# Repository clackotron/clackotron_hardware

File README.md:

# Clackotron 2000 - Hardware
This repository contains the hardware for the Clackotron 2000 project, which provides a simple, all-in-one solution for controlling SBB split-flap modules. For more information on the project in general, visit the [docs repository](https://github.com/clackotron/clackotron_docs).

The hardware is based around an ESP32-S3 and designed in KiCAD 9.x. The production files can be used to easily order the latest version of the PCB from a manufacturer. (JLCPCB)

Most notably, the hardware contains:
* 30V DC input and +/-/A/B connector (same as SBB split flap modules).
* Internal power supply for 5V (RS485) and 3.3V (ESP32-S3).
* An ESP32-S3 on which the [firmware](https://github.com/clackotron/clackotron_firmware) and [webinterface](https://github.com/clackotron/clackotron_webinterface) will run.
* A level converter for sending/receiving RS485 from the ESP32-S3.
* An RTC (PCF85263A) and battery for time-keeping while offline.
* Two buttons and a RGB-Led for misc. functionality.

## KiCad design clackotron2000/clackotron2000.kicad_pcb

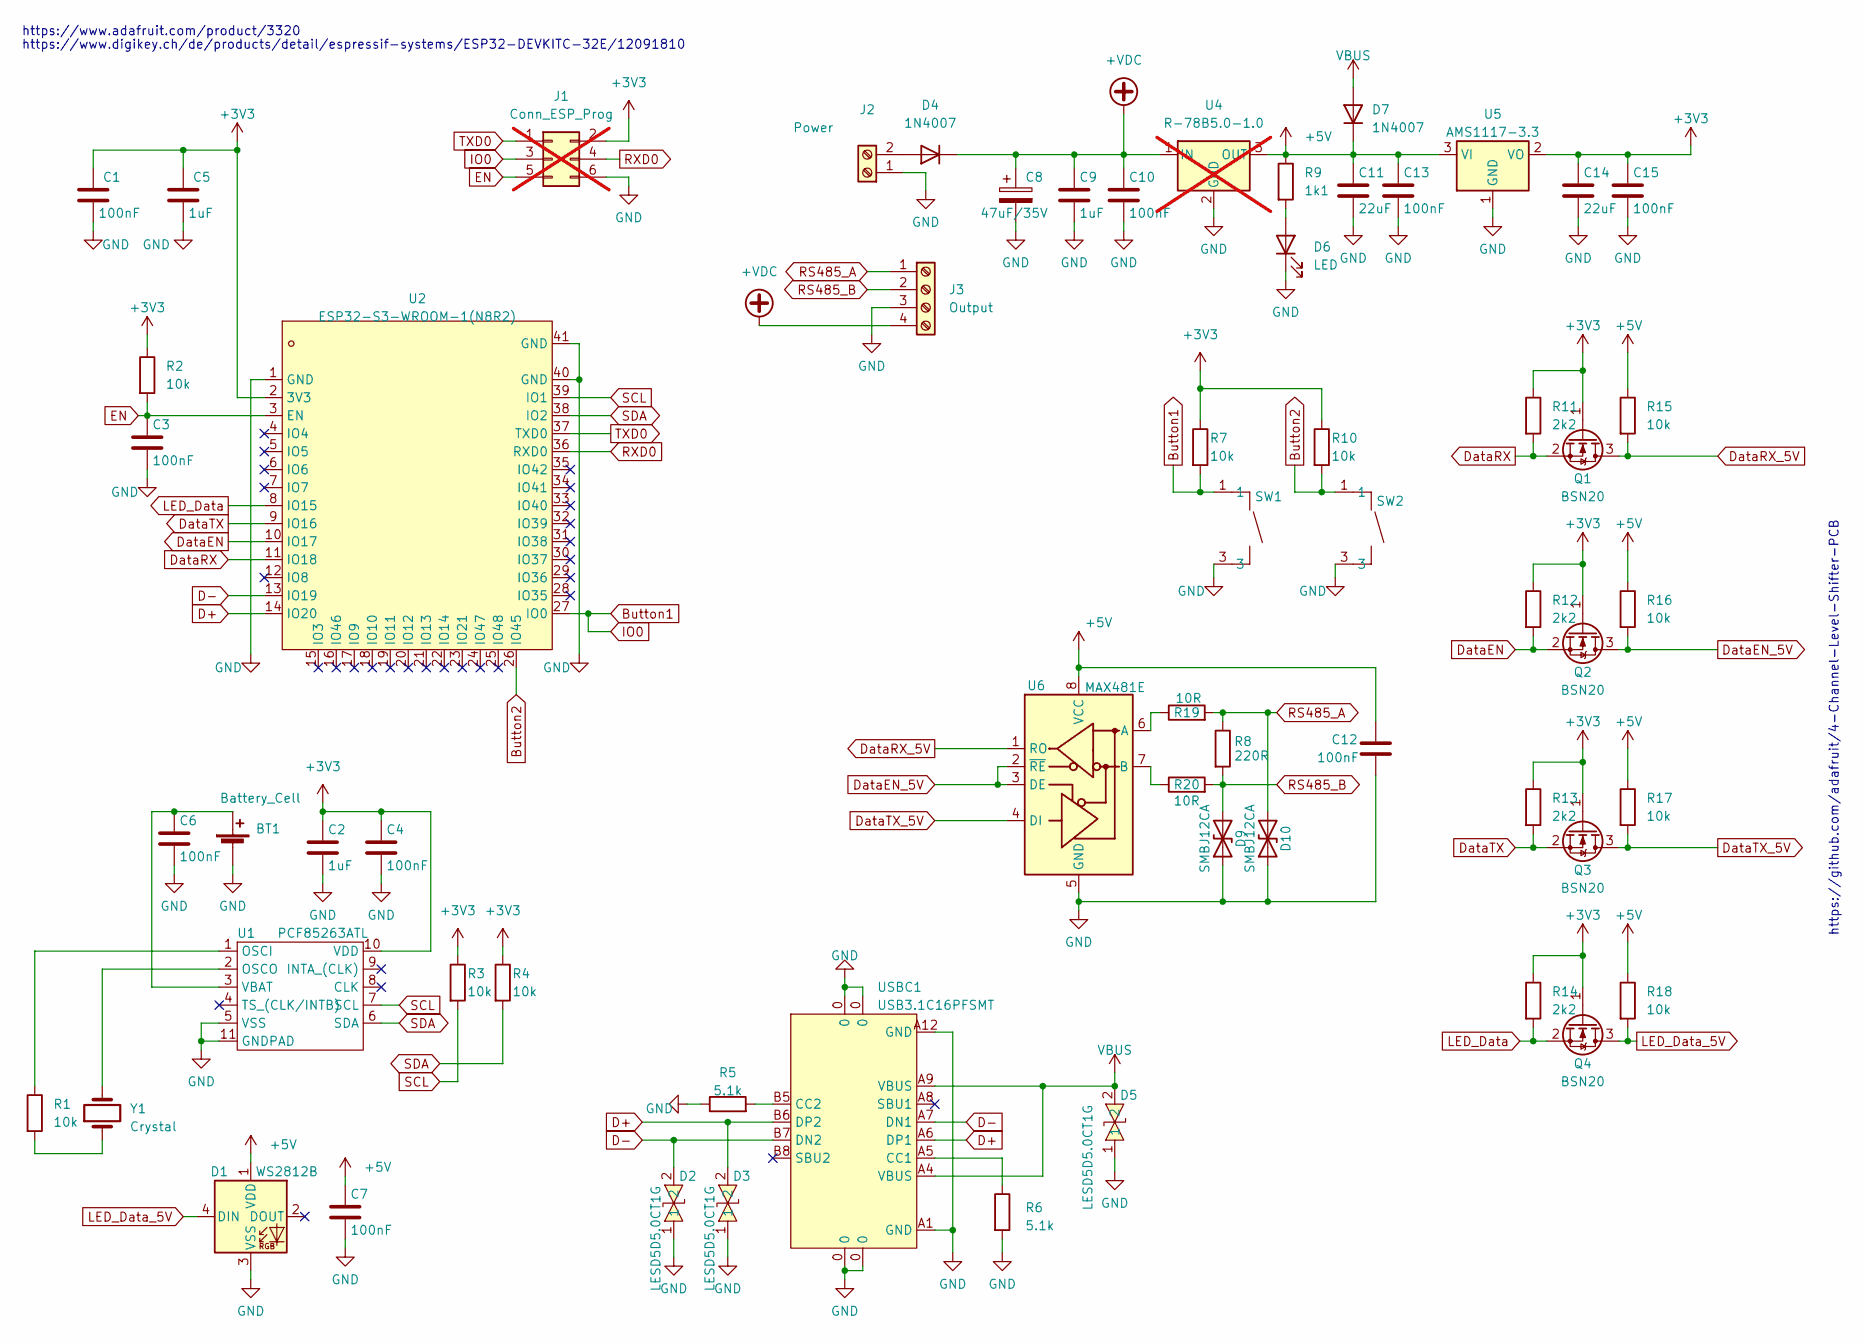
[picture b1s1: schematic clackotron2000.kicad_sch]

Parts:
BT1: Battery_Cell; BAT-SMD_MYOUNG_MY-2032-04; LCSC Part # C964837
C1, C3, C4, C6, C7, C10, C12, C13, C15: 100nF; C_0805_2012Metric; LCSC Part # C49678
C2, C5, C9: 1uF; C_0805_2012Metric; LCSC Part # C28323
C8: 47uF/35V; CAP-SMD_BD6.3-L6.6-W6.6-LS7.2-FD; LCSC Part # C3344
C11, C14: 22uF; C_1206_3216Metric; LCSC Part # C12891
D1: WS2812B; LED_WS2812B_PLCC4_5.0x5.0mm_P3.2mm; LCSC Part # C2761795
D2, D3, D5: LESD5D5.0CT1G; SOD-523_L1.2-W0.8-LS1.6-BI; LCSC Part C383211
D4, D7: 1N4007; D_SMA; LCSC Part # C2909831
D6: LED; LED_0805_2012Metric; LCSC Part # C84256
D9, D10: SMBJ12CA; D_SMB; LCSC Part C83849
J1: Conn_ESP_Prog; PinHeader_2x03_P2.54mm_Vertical; not fitted
J2: Power; TerminalBlock_4Ucon_1x02_P3.50mm_Horizontal; LCSC Part # C466970
J3: Output; TerminalBlock_4Ucon_1x04_P3.50mm_Horizontal; LCSC Part # C557656
Q1, Q2, Q3, Q4: BSN20; SOT-23; LCSC Part # C116157
R1, R2, R3, R4, R7, R10, R15, R16, R17, R18: 10k; R_0805_2012Metric; LCSC Part # C17414
R5, R6: 5.1k; R_0805_2012Metric; LCSC Part # C204548
R8: 220R; R_1206_3216Metric; LCSC Part # C17957
R9: 1k1; R_0805_2012Metric; LCSC Part # C325794
R11, R12, R13, R14: 2k2; R_0805_2012Metric; LCSC Part # C17520
R19, R20: 10R; R_1206_3216Metric; LCSC Part # C840609
SW1, SW2: K2-1102SP-C4SC-04; KEY-SMD_4P-L6.0-W6.0-P4.50-LS9.5-BL; LCSC Part C127509
U1: PCF85263ATL; DFN-10-1EP_2.6x2.6mm_P0.5mm_EP1.3x2.2mm; LCSC Part C2651523
U2: ESP32-S3-WROOM-1(N8R2); WIRELM-SMD_ESP32-S3-WROOM-1; LCSC Part C2913204
U4: R-78B5.0-1.0; Converter_DCDC_RECOM_R-78E-0.5_THT; digikey 945-R-78K5.0-1.0-ND; not fitted
U5: AMS1117-3.3; SOT-223-3_TabPin2; LCSC Part # C369933
U6: MAX481E; SOIC-8_3.9x4.9mm_P1.27mm; LCSC Part C41369525
USBC1: USB3.1C16PFSMT; USB-C-SMD_TYPE-C-USB-17; LCSC Part C167321
Y1: Crystal; Crystal_SMD_3215-2Pin_3.2x1.5mm; LCSC Part # C130253

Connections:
+3V3: C1.1, C2.1, C4.1, C5.1, C14.1, C15.1, J1.2, Q1.1 (G), Q2.1 (G), Q3.1 (G), Q4.1 (G), R2.1, R3.1, R4.1, R7.1, R10.1, R11.1, R12.1, R13.1, R14.1, U1.10 (VDD), U2.2 (3V3), U5.2 (VO)
+5V: C7.1, C11.1, C12.1, C13.1, D1.1 (VDD), D7.1 (K), R9.1, R15.1, R16.1, R17.1, R18.1, U4.3 (OUT), U5.3 (VI), U6.8 (VCC)
+VDC: C8.1, C9.1, C10.1, D4.1 (K), J3.4, U4.1 (IN)
Button1: J1.3, R7.2, SW1.1, SW1.2, U2.27 (IO0)
Button2: R10.2, SW2.1, SW2.2, U2.26 (IO45)
D+: D3.2, U2.14 (IO20), USBC1.A6 (DP1), USBC1.B6 (DP2)
D-: D2.2, U2.13 (IO19), USBC1.A7 (DN1), USBC1.B7 (DN2)
DataEN: Q2.2 (S), R12.2, U2.10 (IO17)
DataEN_5V: Q2.3 (D), R16.2, U6.2 (~RE), U6.3 (DE)
DataRX: Q1.2 (S), R11.2, U2.11 (IO18)
DataRX_5V: Q1.3 (D), R15.2, U6.1 (RO)
DataTX: Q3.2 (S), R13.2, U2.9 (IO16)
DataTX_5V: Q3.3 (D), R17.2, U6.4 (DI)
EN: C3.1, J1.5, R2.2, U2.3 (EN)
GND: BT1.2 (-), C1.2, C2.2, C3.2, C4.2, C5.2, C6.2, C7.2, C8.2, C9.2, C10.2, C11.2, C12.2, C13.2, C14.2, C15.2, D1.3 (VSS), D2.1, D3.1, D5.1, D6.1 (K), D9.1 (A1), D10.1 (A1), J1.6, J2.1, J3.3, R5.1, R6.2, SW1.3, SW1.4, SW2.3, SW2.4, U1.5 (VSS), U1.11 (GNDPAD), U2.1 (GND), U2.40 (GND), U2.41 (GND), U4.2 (GND), U5.1 (GND), U6.5 (GND), USBC1.0, USBC1.A1 (GND), USBC1.A12 (GND)
LED_Data: Q4.2 (S), R14.2, U2.8 (IO15)
LED_Data_5V: D1.4 (DIN), Q4.3 (D), R18.2
unnamed: BT1.1 (+), C6.1, U1.3 (VBAT)
unnamed: D4.2 (A), J2.2
unnamed: D6.2 (A), R9.2
unnamed: R1.2, Y1.1
unnamed: R1.1, U1.1 (OSCI)
unnamed: U1.2 (OSCO), Y1.2
unnamed: R19.1, U6.6 (A)
unnamed: R20.1, U6.7 (B)
unnamed: R6.1, USBC1.A5 (CC1)
unnamed: R5.2, USBC1.B5 (CC2)
RS485_A: D10.2 (A2), J3.1, R8.1, R19.2
RS485_B: D9.2 (A2), J3.2, R8.2, R20.2
RXD0: J1.4, U2.36 (RXD0)
SCL: R3.2, U1.7 (SCL), U2.39 (IO1)
SDA: R4.2, U1.6 (SDA), U2.38 (IO2)
TXD0: J1.1, U2.37 (TXD0)
VBUS: D5.2, D7.2 (A), USBC1.A4 (VBUS), USBC1.A9 (VBUS)

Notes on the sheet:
https://github.com/adafruit/4-Channel-Level-Shifter-PCB
https://www.adafruit.com/product/3320
https://www.digikey.ch/de/products/detail/espressif-systems/ESP32-DEVKITC-32E/12091810

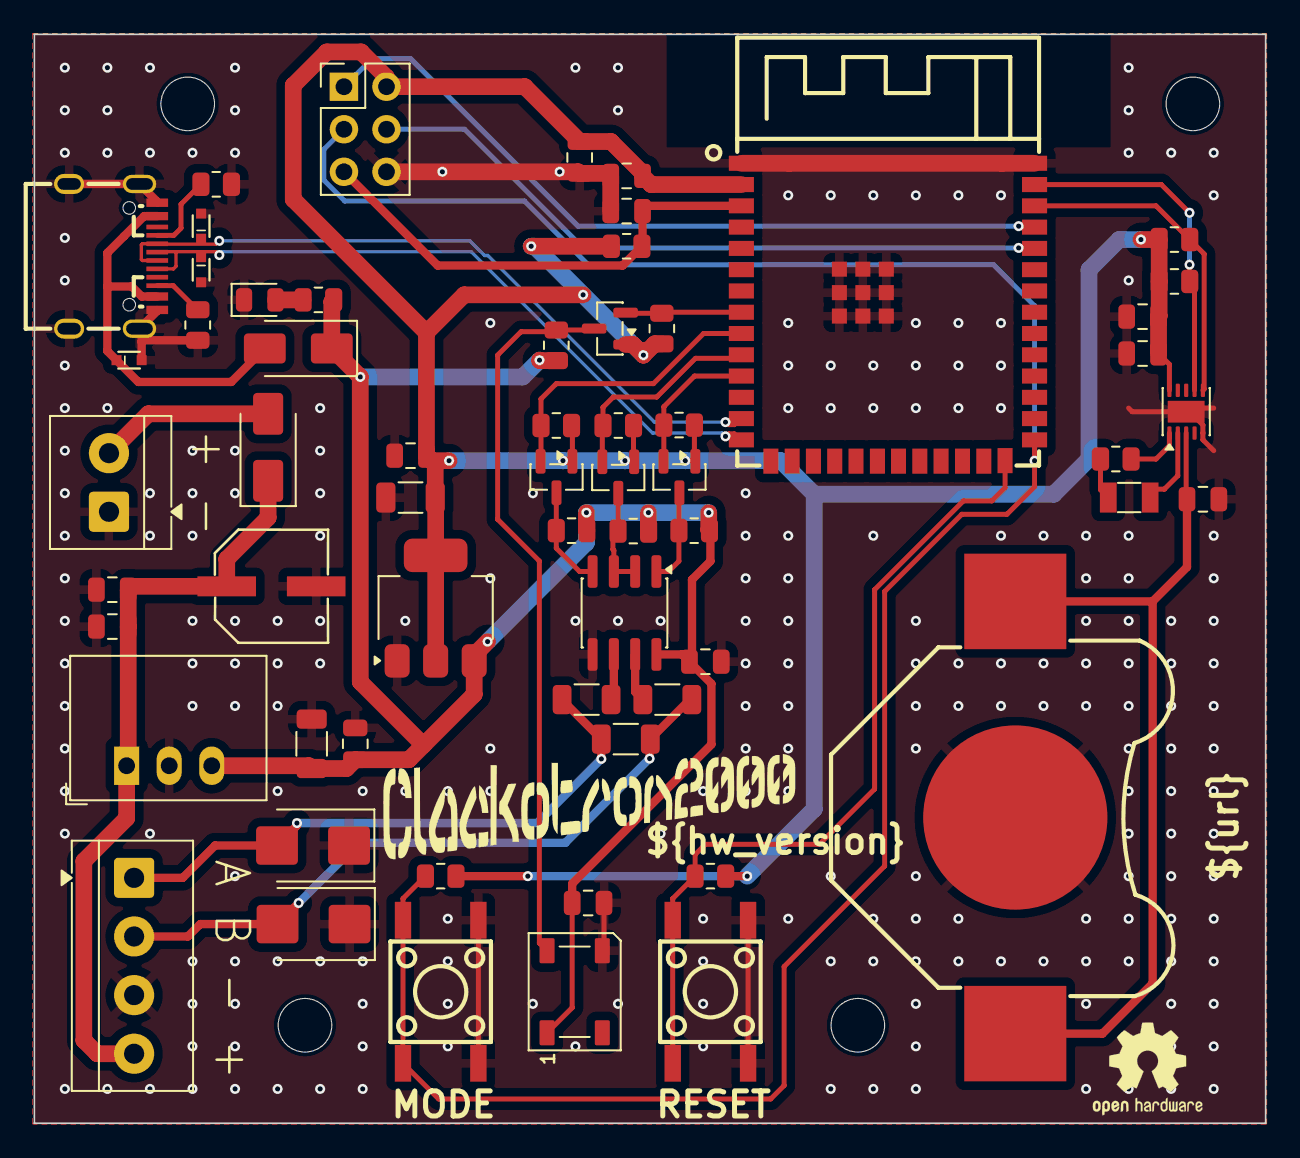
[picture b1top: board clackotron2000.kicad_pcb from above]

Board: 2 copper layers, 73.5 x 65.0 mm, 61 parts (0 on the bottom side), 34 nets.

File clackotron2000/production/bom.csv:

Designator,Footprint,Quantity,Value,LCSC Part #
BT1,BAT-SMD_MYOUNG_MY-2032-04,1,Battery_Cell,C964837
"C1, C10, C12, C13, C15, C3, C4, C6, C7",0805,9,100nF,C49678
"C11, C14",1206,2,22uF,C12891
"C2, C5, C9",0805,3,1uF,C28323
C8,CAP-SMD_BD6.3-L6.6-W6.6-LS7.2-FD,1,47uF/35V,C3344
D1,LED_WS2812B_PLCC4_5.0x5.0mm_P3.2mm,1,WS2812B,C2761795
"D2, D3, D5",SOD-523_L1.2-W0.8-LS1.6-BI,3,LESD5D5.0CT1G,C383211
"D4, D7",D_SMA,2,1N4007,C2909831
D6,0805,1,LED,C84256
J2,TerminalBlock_4Ucon_1x02_P3.50mm_Horizontal,1,Power,C466970
J3,TerminalBlock_4Ucon_1x04_P3.50mm_Horizontal,1,Output,C98769
"Q1, Q2, Q3, Q4",SOT-23,4,BSN20,C116157
"R1, R10, R15, R16, R17, R18, R2, R3, R4, R7",0805,10,10k,C17414
"R11, R12, R13, R14",0805,4,2k2,C17520
"R5, R6",0805,2,5.1k,C17414
R8,1206,1,220R,C17957
R9,0805,1,1k1,C17375
"SW1, SW2",KEY-SMD_4P-L6.0-W6.0-P4.50-LS9.5-BL,2,K2-1102SP-C4SC-04,C127509
U1,TSSOP-8_3x3mm_P0.65mm,1,PCF85263ATT,C2651543
U2,WIRELM-SMD_ESP32-S3-WROOM-1,1,ESP32-S3-WROOM-1(N8R2),C2913204
U3,SOIC-8_3.9x4.9mm_P1.27mm,1,SP3485EN,C5279038
U5,SOT-223-3_TabPin2,1,AMS1117-3.3,C369933
USBC1,USB-C-SMD_TYPE-C-USB-17,1,USB3.1C16PFSMT,C167321
Y1,Crystal_SMD_3215-2Pin_3.2x1.5mm,1,Crystal,C515342

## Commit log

2023-06-12 chore: rebase changes from internal repository
2023-06-13 Add new parts for next hardware revision
2023-06-13 add new parts for next hardware revision to schematic
2023-06-14 hardware redesign for v3.0 done
2023-06-20 generate production data and fix some part numbers and stuff
2023-06-25 add oshw logo and fix some pcb part configs
2023-06-25 change gitignore to include all production files!
2023-11-21 add new parts. not yet done...
2023-11-22 changed all parts. set to version 3.1
2024-01-10 remove lock file
2026-01-21 improve voltage safety margins of outputs
    - change rs485 transceiver to other model (successor of the one used in the original splitflap board)
    - add tvs diodes to rs485 lines
    - add series resistors to rs485 lines
2026-01-22 add lock file to gitignore
